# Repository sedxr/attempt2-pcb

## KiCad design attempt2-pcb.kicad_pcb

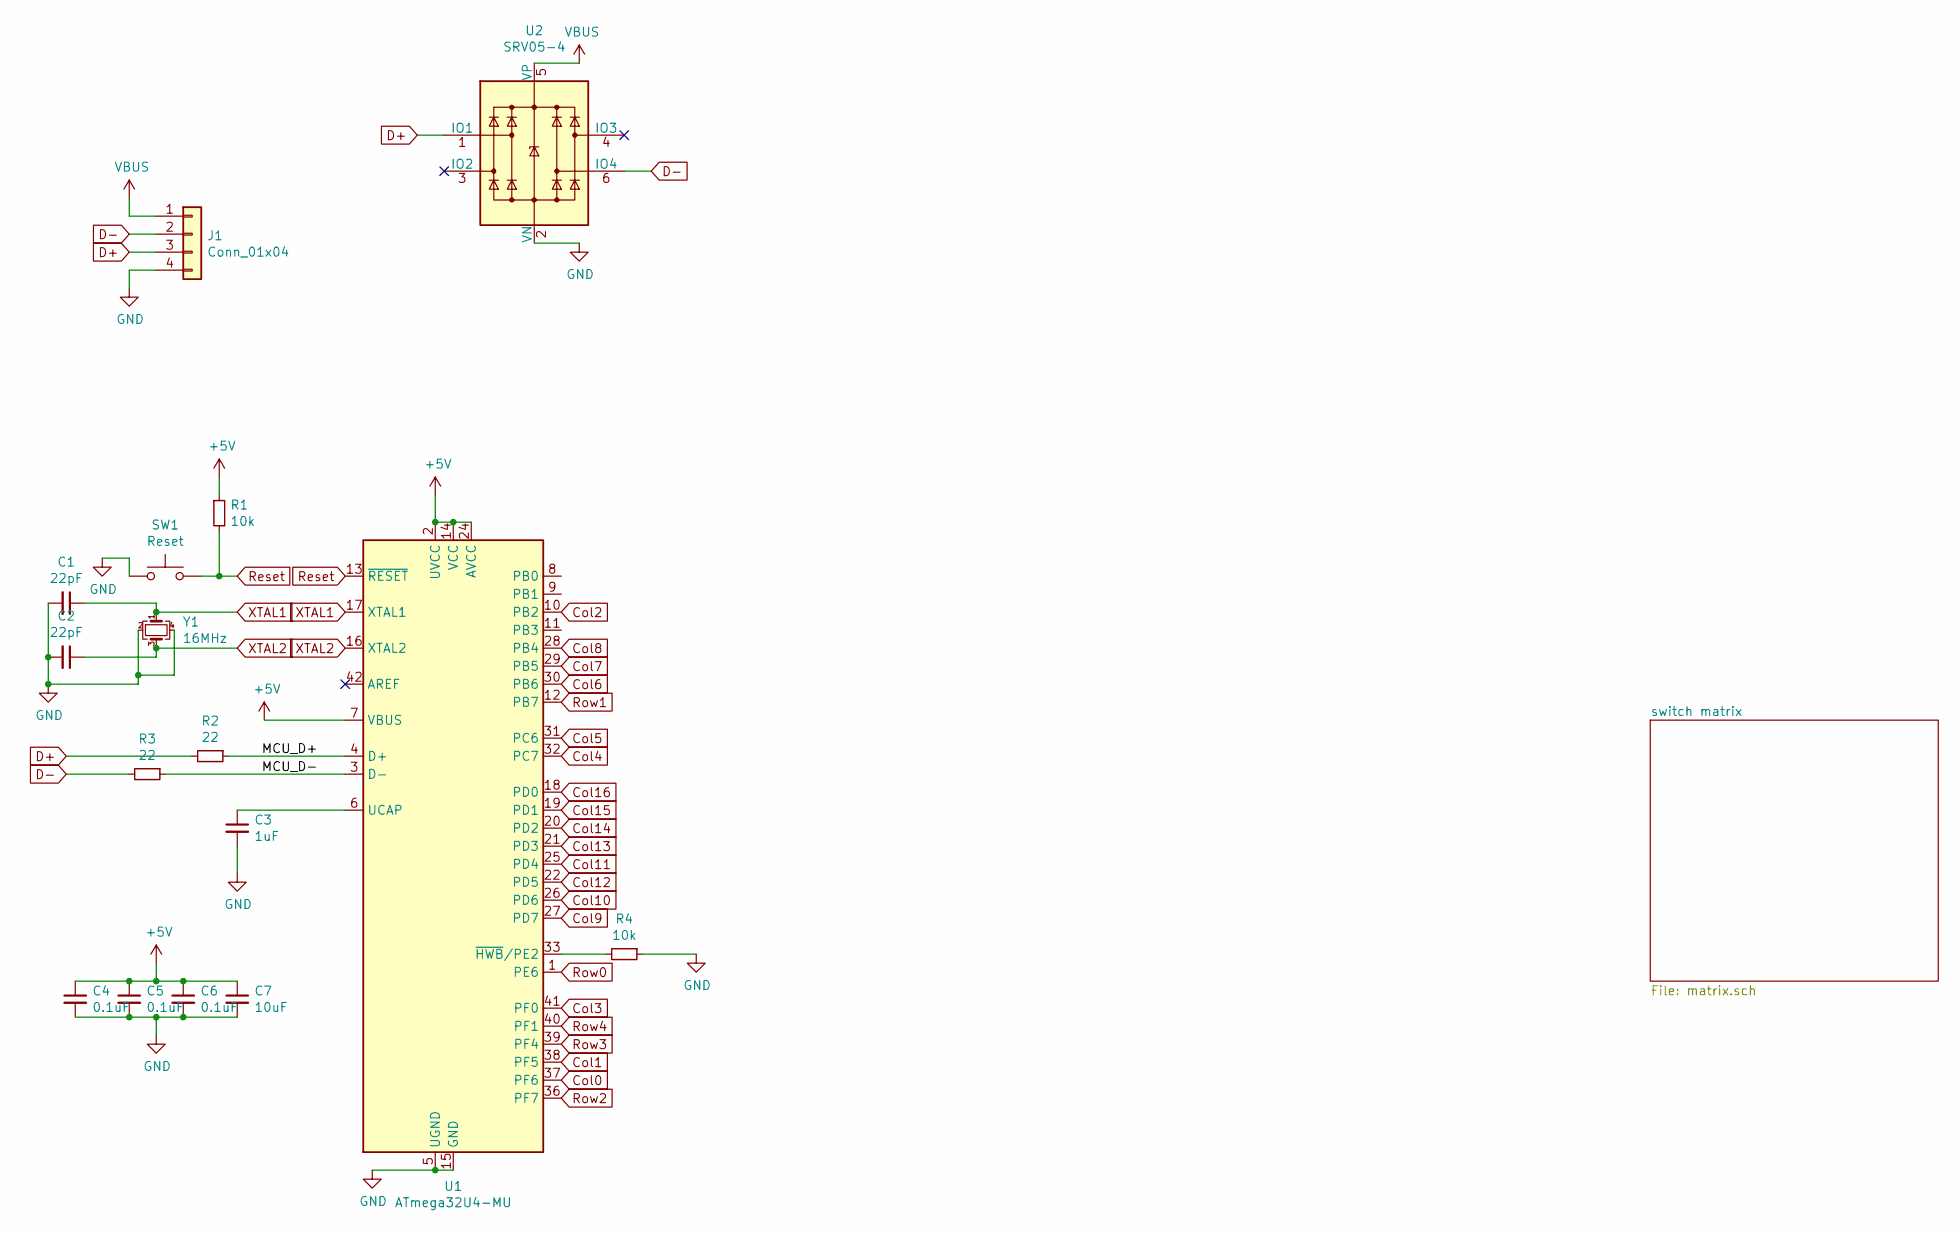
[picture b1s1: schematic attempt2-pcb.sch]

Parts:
C1, C2: 22pF; C_0805_2012Metric
C3: 1uF; C_0805_2012Metric
C4, C5, C6: 0.1uF; C_0805_2012Metric
C7: 10uF; C_0805_2012Metric
J1: Conn_01x04; JST-SR-4
R1, R4: 10k; R_0805_2012Metric
R2, R3: 22; R_0805_2012Metric
SW1: Reset; SKQG-1155865
U1: ATmega32U4-MU; QFN-44-1EP_7x7mm_P0.5mm_EP5.2x5.2mm
U2: SRV05-4; SOT-23-6
Y1: 16MHz; Crystal_SMD_3225-4Pin_3.2x2.5mm

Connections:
+5V: C4.1, C5.1, C6.1, C7.1, R1.1, U1.2 (UVCC), U1.7 (VBUS), U1.14 (VCC), U1.24 (AVCC), U1.34 (VCC), U1.44 (AVCC)
/MCU_D+: R2.1, U1.4 (D+)
/MCU_D-: R3.1, U1.3 (D-)
Col0: U1.37 (PF6); also elsewhere on the board
Col1: U1.38 (PF5); also elsewhere on the board
Col2: U1.10 (PB2); also elsewhere on the board
Col3: U1.41 (PF0); also elsewhere on the board
Col4: U1.32 (PC7); also elsewhere on the board
Col5: U1.31 (PC6); also elsewhere on the board
Col6: U1.30 (PB6); also elsewhere on the board
Col7: U1.29 (PB5); also elsewhere on the board
Col8: U1.28 (PB4); also elsewhere on the board
Col9: U1.27 (PD7); also elsewhere on the board
Col10: U1.26 (PD6); also elsewhere on the board
Col11: U1.25 (PD4); also elsewhere on the board
Col12: U1.22 (PD5); also elsewhere on the board
Col13: U1.21 (PD3); also elsewhere on the board
Col14: U1.20 (PD2); also elsewhere on the board
Col15: U1.19 (PD1); also elsewhere on the board
Col16: U1.18 (PD0); also elsewhere on the board
D+: J1.3, R2.2, U2.1 (IO1)
D-: J1.2, R3.2, U2.6 (IO4)
GND: C1.2, C2.2, C3.2, C4.2, C5.2, C6.2, C7.2, J1.4, R4.1, SW1.1, U1.5 (UGND), U1.15 (GND), U1.23 (GND), U1.35 (GND), U1.43 (GND), U1.45 (GND), U2.2 (VN), Y1.2, Y1.4
unnamed: C3.1, U1.6 (UCAP)
unnamed: R4.2, U1.33 (~HWB~/PE2)
Reset: R1.2, SW1.2, U1.13 (~RESET)
Row0: U1.1 (PE6); also elsewhere on the board
Row1: U1.12 (PB7); also elsewhere on the board
Row2: U1.36 (PF7); also elsewhere on the board
Row3: U1.39 (PF4); also elsewhere on the board
Row4: U1.40 (PF1); also elsewhere on the board
VBUS: J1.1, U2.5 (VP)
XTAL1: C1.1, U1.17 (XTAL1), Y1.1
XTAL2: C2.1, U1.16 (XTAL2), Y1.3

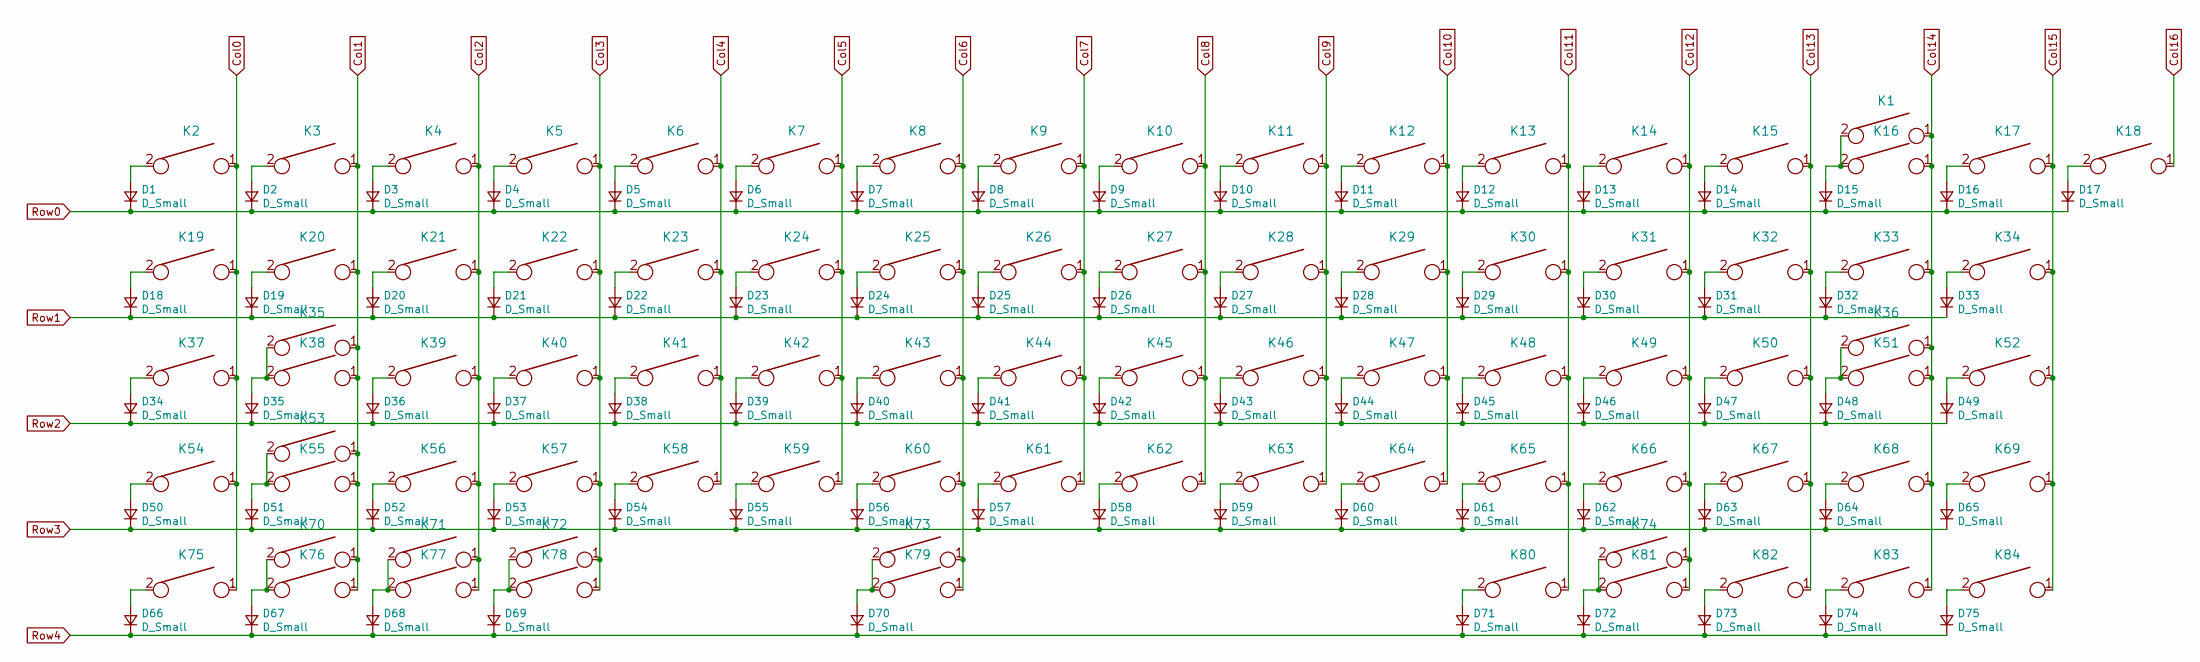
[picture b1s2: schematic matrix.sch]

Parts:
D1, D2, D3, D4, D5, D6, D7, D8, D9, D10, D11, D12, D13, D14, D15, D16, D17, D18, D19, D20, D21, D22, D23, D24, D25, D26, D27, D28, D29, D30, D31, D32, D33, D34, D35, D36, D37, D38, D39, D40, D41, D42, D43, D44, D45, D46, D47, D48, D49, D50, D51, D52, D53, D54, D55, D56, D57, D58, D59, D60, D61, D62, D63, D64, D65, D66, D67, D68, D69, D70, D71, D72, D73, D74, D75: D_Small; D_SOD-123
K1, K2, K3, K4, K5, K6, K7, K8, K9, K10, K11, K12, K13, K14, K15, K17, K18, K19, K21, K22, K23, K24, K25, K26, K27, K28, K29, K30, K31, K32, K34, K37, K39, K40, K41, K42, K43, K44, K45, K46, K47, K48, K49, K50, K52, K54, K56, K57, K58, K59, K60, K61, K62, K63, K64, K65, K66, K68, K69, K71, K75, K82, K83, K84: keyboard_parts_KEYSW; MXOnly-1U-NoLED
K16: keyboard_parts_KEYSW; MXOnly-2U-NoLED
K20, K33, K76, K78, K81: keyboard_parts_KEYSW; MXOnly-1.5U-NoLED
K35, K53, K70, K72, K74, K77, K80: keyboard_parts_KEYSW; MXOnly-1.25U-NoLED
K36: keyboard_parts_KEYSW; MXOnly-ISO-NoLED
K38, K67: keyboard_parts_KEYSW; MXOnly-1.75U-NoLED
K51, K55: keyboard_parts_KEYSW; MXOnly-2.25U-NoLED
K73: keyboard_parts_KEYSW; MXOnly-6.25U-ReversedStabilizers-NoLED
K79: keyboard_parts_KEYSW; MXOnly-7U-ReversedStabilizers-NoLED

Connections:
Col0: K2.1, K19.1, K37.1, K54.1, K75.1; also elsewhere on the board
Col1: K3.1, K20.1, K35.1, K38.1, K53.1, K55.1, K70.1, K76.1; also elsewhere on the board
Col2: K4.1, K21.1, K39.1, K56.1, K71.1, K77.1; also elsewhere on the board
Col3: K5.1, K22.1, K40.1, K57.1, K72.1, K78.1; also elsewhere on the board
Col4: K6.1, K23.1, K41.1, K58.1; also elsewhere on the board
Col5: K7.1, K24.1, K42.1, K59.1; also elsewhere on the board
Col6: K8.1, K25.1, K43.1, K60.1, K73.1, K79.1; also elsewhere on the board
Col7: K9.1, K26.1, K44.1, K61.1; also elsewhere on the board
Col8: K10.1, K27.1, K45.1, K62.1; also elsewhere on the board
Col9: K11.1, K28.1, K46.1, K63.1; also elsewhere on the board
Col10: K12.1, K29.1, K47.1, K64.1; also elsewhere on the board
Col11: K13.1, K30.1, K48.1, K65.1, K80.1; also elsewhere on the board
Col12: K14.1, K31.1, K49.1, K66.1, K74.1, K81.1; also elsewhere on the board
Col13: K15.1, K32.1, K50.1, K67.1, K82.1; also elsewhere on the board
Col14: K1.1, K16.1, K33.1, K36.1, K51.1, K68.1, K83.1; also elsewhere on the board
Col15: K17.1, K34.1, K52.1, K69.1, K84.1; also elsewhere on the board
Col16: K18.1; also elsewhere on the board
unnamed: D1.2 (A), K2.2
unnamed: D2.2 (A), K3.2
unnamed: D3.2 (A), K4.2
unnamed: D4.2 (A), K5.2
unnamed: D5.2 (A), K6.2
unnamed: D6.2 (A), K7.2
unnamed: D7.2 (A), K8.2
unnamed: D8.2 (A), K9.2
unnamed: D9.2 (A), K10.2
unnamed: D10.2 (A), K11.2
unnamed: D11.2 (A), K12.2
unnamed: D12.2 (A), K13.2
unnamed: D13.2 (A), K14.2
unnamed: D14.2 (A), K15.2
unnamed: D15.2 (A), K1.2, K16.2
unnamed: D16.2 (A), K17.2
unnamed: D17.2 (A), K18.2
unnamed: D18.2 (A), K19.2
unnamed: D19.2 (A), K20.2
unnamed: D20.2 (A), K21.2
unnamed: D21.2 (A), K22.2
unnamed: D22.2 (A), K23.2
unnamed: D23.2 (A), K24.2
unnamed: D24.2 (A), K25.2
unnamed: D25.2 (A), K26.2
unnamed: D26.2 (A), K27.2
unnamed: D27.2 (A), K28.2
unnamed: D28.2 (A), K29.2
unnamed: D29.2 (A), K30.2
unnamed: D30.2 (A), K31.2
unnamed: D31.2 (A), K32.2
unnamed: D32.2 (A), K33.2
unnamed: D33.2 (A), K34.2
unnamed: D34.2 (A), K37.2
unnamed: D35.2 (A), K35.2, K38.2
unnamed: D36.2 (A), K39.2
unnamed: D37.2 (A), K40.2
unnamed: D38.2 (A), K41.2
unnamed: D39.2 (A), K42.2
unnamed: D40.2 (A), K43.2
unnamed: D41.2 (A), K44.2
unnamed: D42.2 (A), K45.2
unnamed: D43.2 (A), K46.2
unnamed: D44.2 (A), K47.2
unnamed: D45.2 (A), K48.2
unnamed: D46.2 (A), K49.2
unnamed: D47.2 (A), K50.2
unnamed: D48.2 (A), K36.2, K51.2
unnamed: D49.2 (A), K52.2
unnamed: D50.2 (A), K54.2
unnamed: D51.2 (A), K53.2, K55.2
unnamed: D52.2 (A), K56.2
unnamed: D53.2 (A), K57.2
unnamed: D54.2 (A), K58.2
unnamed: D55.2 (A), K59.2
unnamed: D56.2 (A), K60.2
unnamed: D57.2 (A), K61.2
unnamed: D58.2 (A), K62.2
unnamed: D59.2 (A), K63.2
unnamed: D60.2 (A), K64.2
unnamed: D61.2 (A), K65.2
unnamed: D62.2 (A), K66.2
unnamed: D63.2 (A), K67.2
unnamed: D64.2 (A), K68.2
unnamed: D65.2 (A), K69.2
unnamed: D66.2 (A), K75.2
unnamed: D67.2 (A), K70.2, K76.2
unnamed: D68.2 (A), K71.2, K77.2
unnamed: D69.2 (A), K72.2, K78.2
unnamed: D70.2 (A), K73.2, K79.2
unnamed: D71.2 (A), K80.2
unnamed: D72.2 (A), K74.2, K81.2
unnamed: D73.2 (A), K82.2
unnamed: D74.2 (A), K83.2
unnamed: D75.2 (A), K84.2
Row0: D1.1 (K), D2.1 (K), D3.1 (K), D4.1 (K), D5.1 (K), D6.1 (K), D7.1 (K), D8.1 (K), D9.1 (K), D10.1 (K), D11.1 (K), D12.1 (K), D13.1 (K), D14.1 (K), D15.1 (K), D16.1 (K), D17.1 (K); also elsewhere on the board
Row1: D18.1 (K), D19.1 (K), D20.1 (K), D21.1 (K), D22.1 (K), D23.1 (K), D24.1 (K), D25.1 (K), D26.1 (K), D27.1 (K), D28.1 (K), D29.1 (K), D30.1 (K), D31.1 (K), D32.1 (K), D33.1 (K); also elsewhere on the board
Row2: D34.1 (K), D35.1 (K), D36.1 (K), D37.1 (K), D38.1 (K), D39.1 (K), D40.1 (K), D41.1 (K), D42.1 (K), D43.1 (K), D44.1 (K), D45.1 (K), D46.1 (K), D47.1 (K), D48.1 (K), D49.1 (K); also elsewhere on the board
Row3: D50.1 (K), D51.1 (K), D52.1 (K), D53.1 (K), D54.1 (K), D55.1 (K), D56.1 (K), D57.1 (K), D58.1 (K), D59.1 (K), D60.1 (K), D61.1 (K), D62.1 (K), D63.1 (K), D64.1 (K), D65.1 (K); also elsewhere on the board
Row4: D66.1 (K), D67.1 (K), D68.1 (K), D69.1 (K), D70.1 (K), D71.1 (K), D72.1 (K), D73.1 (K), D74.1 (K), D75.1 (K); also elsewhere on the board

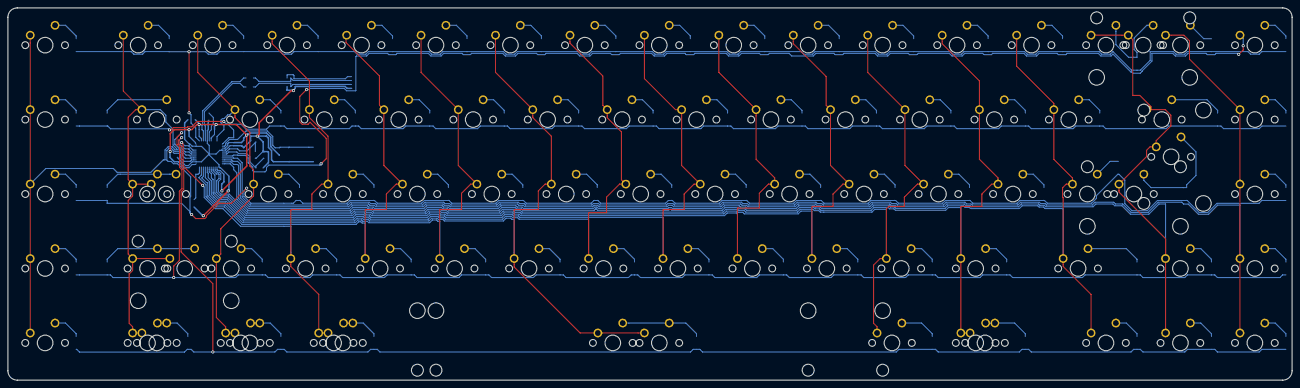
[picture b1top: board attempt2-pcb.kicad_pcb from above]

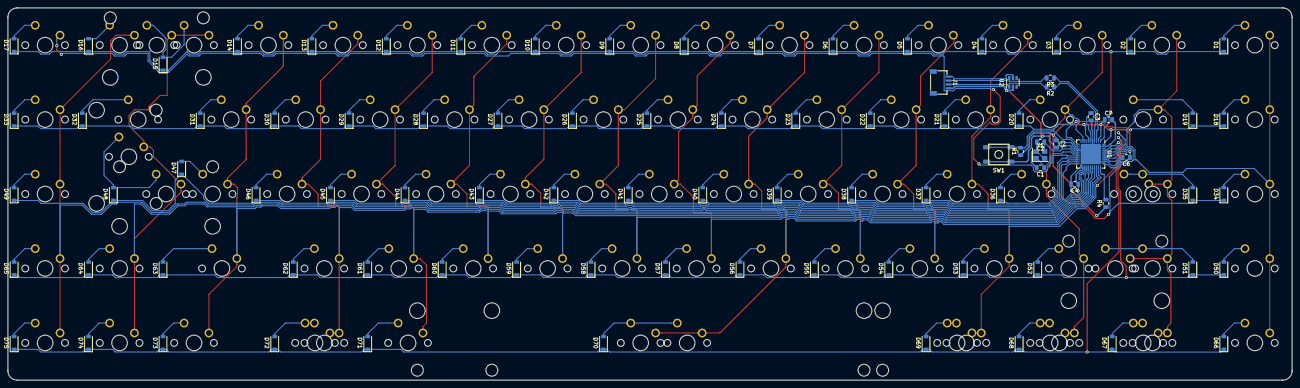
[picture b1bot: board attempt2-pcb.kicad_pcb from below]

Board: 2 copper layers, 328.6 x 95.3 mm, 175 parts (91 on the bottom side), 109 nets.

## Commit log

2022-03-07 Initialize project
2022-03-08 Add submodules
2022-03-08 Add footprint libraries
2022-03-08 Create _autosave-attempt2-pcb.sch
    Save
2022-03-09 Switch matrix save
2022-03-10 Switch matrix save
    restarted and cleaned up matrix
    added split backspace support
2022-03-10 Switch Matrix Save
    switch matrix almost done
2022-03-11 Schematic Finished
2022-03-11 PCB Preparations Finished
    routing time
    so fun
2022-03-11 PCB prep actually finished
2022-03-11 save
2022-03-12 Rough Draft Finished
2022-03-12 Fill Zones
2022-03-12 proofing
2022-03-24 Big Changes
2022-03-24 Gerbers
